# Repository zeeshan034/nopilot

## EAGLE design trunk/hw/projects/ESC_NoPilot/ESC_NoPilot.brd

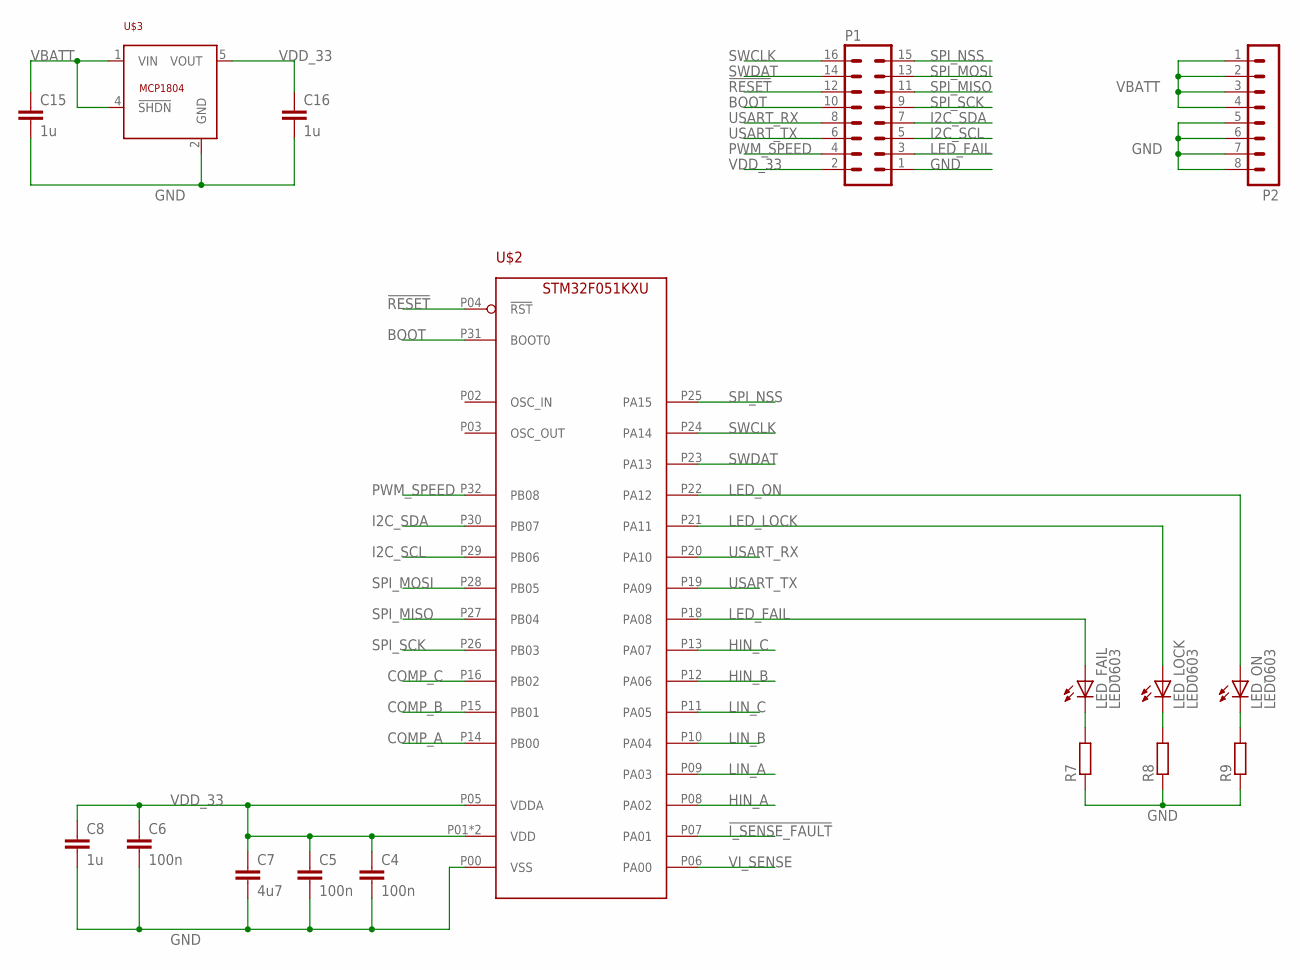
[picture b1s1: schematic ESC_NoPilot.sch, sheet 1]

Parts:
C4, C5, C6: 100n; C0402
C7: 4u7; C0805
C8, C15, C16: 1u; C0805
LED_FAIL: LED0603; D0603
LED_LOCK: LED0603; D0603
LED_ON: LED0603; D0603
P1: MA08-2
P2: MA08-1
R7, R8, R9: R-EU_R0402; R0402
U$2: STM32F051KXU; UFQFPN32
U$3: MCP1804; SOT23

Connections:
!I_SENSE_FAULT: U$2.P07 (PA01); also elsewhere on the board
!RESET: P1.12, U$2.P04 (!RST)
BOOT: P1.10, U$2.P31 (BOOT0)
COMP_A: U$2.P14 (PB00); also elsewhere on the board
COMP_B: U$2.P15 (PB01); also elsewhere on the board
COMP_C: U$2.P16 (PB02); also elsewhere on the board
GND: C4.2, C5.2, C6.2, C7.2, C8.2, C15.2, C16.2, P1.1, P2.5, P2.6, P2.7, P2.8, R7.1, R8.1, R9.1, U$2.P00 (VSS), U$3.2 (GND); also elsewhere on the board
HIN_A: U$2.P08 (PA02); also elsewhere on the board
HIN_B: U$2.P12 (PA06); also elsewhere on the board
HIN_C: U$2.P13 (PA07); also elsewhere on the board
I2C_SCL: P1.5, U$2.P29 (PB06)
I2C_SDA: P1.7, U$2.P30 (PB07)
LED_FAIL: LED_FAIL.A, P1.3, U$2.P18 (PA08)
LED_LOCK: LED_LOCK.A, U$2.P21 (PA11)
LED_ON: LED_ON.A, U$2.P22 (PA12)
LIN_A: U$2.P09 (PA03); also elsewhere on the board
LIN_B: U$2.P10 (PA04); also elsewhere on the board
LIN_C: U$2.P11 (PA05); also elsewhere on the board
unnamed: LED_FAIL.C, R7.2
unnamed: LED_LOCK.C, R8.2
unnamed: LED_ON.C, R9.2
PWM_SPEED: P1.4, U$2.P32 (PB08)
SPI_MISO: P1.11, U$2.P27 (PB04)
SPI_MOSI: P1.13, U$2.P28 (PB05)
SPI_NSS: P1.15, U$2.P25 (PA15)
SPI_SCK: P1.9, U$2.P26 (PB03)
SWCLK: P1.16, U$2.P24 (PA14)
SWDAT: P1.14, U$2.P23 (PA13)
USART_RX: P1.8, U$2.P20 (PA10)
USART_TX: P1.6, U$2.P19 (PA09)
VBATT: C15.1, P2.1, P2.2, P2.3, P2.4, U$3.1 (VIN), U$3.4 (!SHDN); also elsewhere on the board
VDD_33: C4.1, C5.1, C6.1, C7.1, C8.1, C16.1, P1.2, U$2.P01 (VDD), U$2.P05 (VDDA), U$2.P17 (VDD), U$3.5 (VOUT); also elsewhere on the board
VI_SENSE: U$2.P06 (PA00); also elsewhere on the board

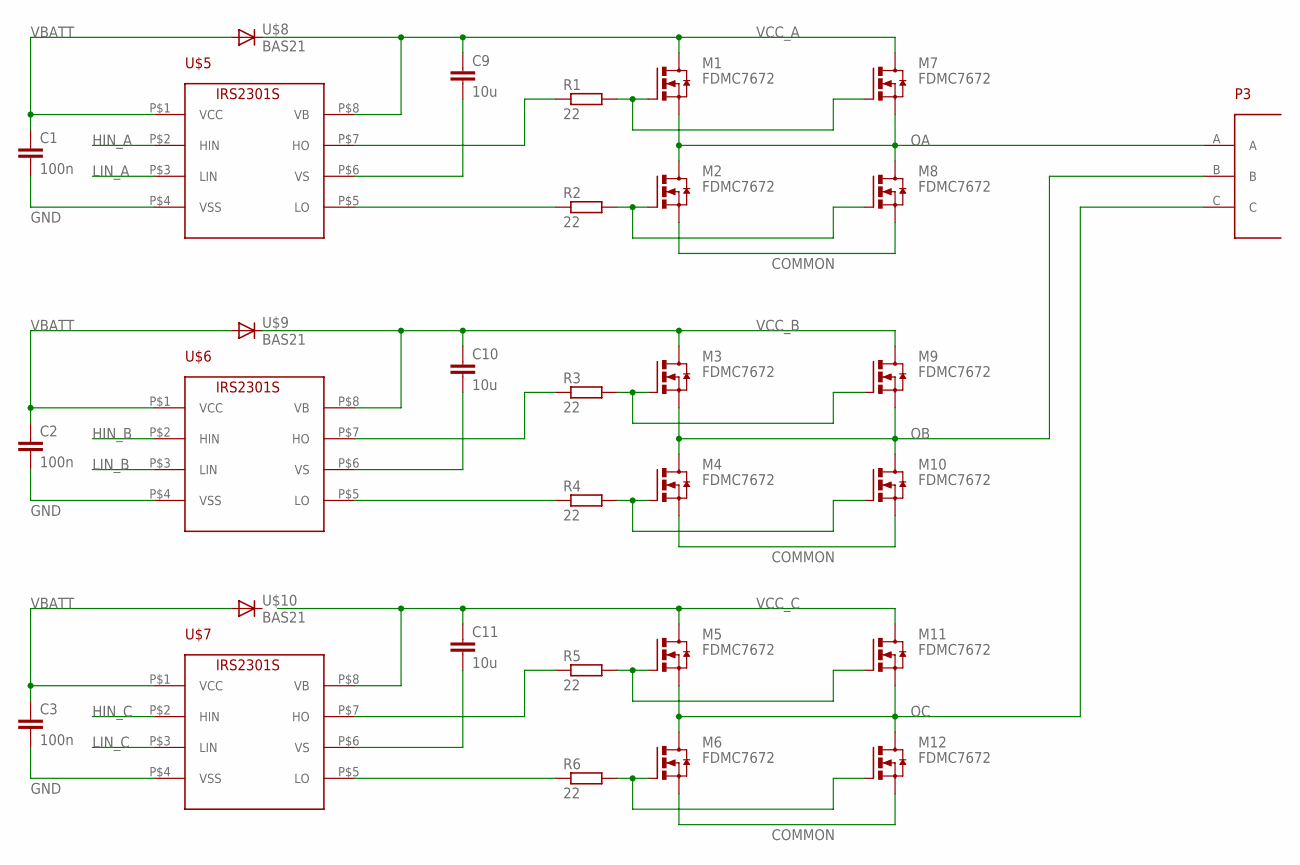
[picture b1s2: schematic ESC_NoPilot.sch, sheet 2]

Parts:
C1, C2, C3: 100n; C0402
C9, C10, C11: 10u; C0805
M1, M2, M3, M4, M5, M6, M7, M8, M9, M10, M11, M12: FDMC7672; MLP_3P3X3P3
P3: 3PH_SJ
R1, R2, R3, R4, R5, R6: 22; R0402
U$5, U$6, U$7: IRS2301S; SOIC8
U$8, U$9, U$10: BAS21; SOT23-3

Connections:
COMMON: M2.P1 (S), M2.P2 (S), M2.P3 (S), M4.P1 (S), M4.P2 (S), M4.P3 (S), M6.P1 (S), M6.P2 (S), M6.P3 (S), M8.P1 (S), M8.P2 (S), M8.P3 (S), M10.P1 (S), M10.P2 (S), M10.P3 (S), M12.P1 (S), M12.P2 (S), M12.P3 (S); also elsewhere on the board
GND: C1.2, C2.2, C3.2, U$5.P$4 (VSS), U$6.P$4 (VSS), U$7.P$4 (VSS); also elsewhere on the board
HIN_A: U$5.P$2 (HIN); also elsewhere on the board
HIN_B: U$6.P$2 (HIN); also elsewhere on the board
HIN_C: U$7.P$2 (HIN); also elsewhere on the board
LIN_A: U$5.P$3 (LIN); also elsewhere on the board
LIN_B: U$6.P$3 (LIN); also elsewhere on the board
LIN_C: U$7.P$3 (LIN); also elsewhere on the board
M1: M1.P4 (G), M7.P4 (G), R1.2
M4: M4.P4 (G), M10.P4 (G), R4.2
unnamed: C9.2, U$5.P$6 (VS)
unnamed: R1.1, U$5.P$7 (HO)
unnamed: M2.P4 (G), M8.P4 (G), R2.2
unnamed: R2.1, U$5.P$5 (LO)
unnamed: C10.2, U$6.P$6 (VS)
unnamed: M3.P4 (G), M9.P4 (G), R3.2
unnamed: R3.1, U$6.P$7 (HO)
unnamed: R4.1, U$6.P$5 (LO)
unnamed: C11.2, U$7.P$6 (VS)
unnamed: R5.1, U$7.P$7 (HO)
unnamed: M5.P4 (G), M11.P4 (G), R5.2
unnamed: M6.P4 (G), M12.P4 (G), R6.2
unnamed: R6.1, U$7.P$5 (LO)
OA: M1.P1 (S), M1.P2 (S), M1.P3 (S), M2.P0 (D), M2.P5 (D), M2.P6 (D), M2.P7 (D), M2.P8 (D), M7.P1 (S), M7.P2 (S), M7.P3 (S), M8.P0 (D), M8.P5 (D), M8.P6 (D), M8.P7 (D), M8.P8 (D), P3.A; also elsewhere on the board
OB: M3.P1 (S), M3.P2 (S), M3.P3 (S), M4.P0 (D), M4.P5 (D), M4.P6 (D), M4.P7 (D), M4.P8 (D), M9.P1 (S), M9.P2 (S), M9.P3 (S), M10.P0 (D), M10.P5 (D), M10.P6 (D), M10.P7 (D), M10.P8 (D), P3.B; also elsewhere on the board
OC: M5.P1 (S), M5.P2 (S), M5.P3 (S), M6.P0 (D), M6.P5 (D), M6.P6 (D), M6.P7 (D), M6.P8 (D), M11.P1 (S), M11.P2 (S), M11.P3 (S), M12.P0 (D), M12.P5 (D), M12.P6 (D), M12.P7 (D), M12.P8 (D), P3.C; also elsewhere on the board
VBATT: C1.1, C2.1, C3.1, U$5.P$1 (VCC), U$6.P$1 (VCC), U$7.P$1 (VCC), U$8.P1 (A), U$9.P1 (A), U$10.P1 (A); also elsewhere on the board
VCC_A: C9.1, M1.P0 (D), M1.P5 (D), M1.P6 (D), M1.P7 (D), M1.P8 (D), M7.P0 (D), M7.P5 (D), M7.P6 (D), M7.P7 (D), M7.P8 (D), U$5.P$8 (VB), U$8.P3 (C)
VCC_B: C10.1, M3.P0 (D), M3.P5 (D), M3.P6 (D), M3.P7 (D), M3.P8 (D), M9.P0 (D), M9.P5 (D), M9.P6 (D), M9.P7 (D), M9.P8 (D), U$6.P$8 (VB), U$9.P3 (C)
VCC_C: C11.1, M5.P0 (D), M5.P5 (D), M5.P6 (D), M5.P7 (D), M5.P8 (D), M11.P0 (D), M11.P5 (D), M11.P6 (D), M11.P7 (D), M11.P8 (D), U$7.P$8 (VB)

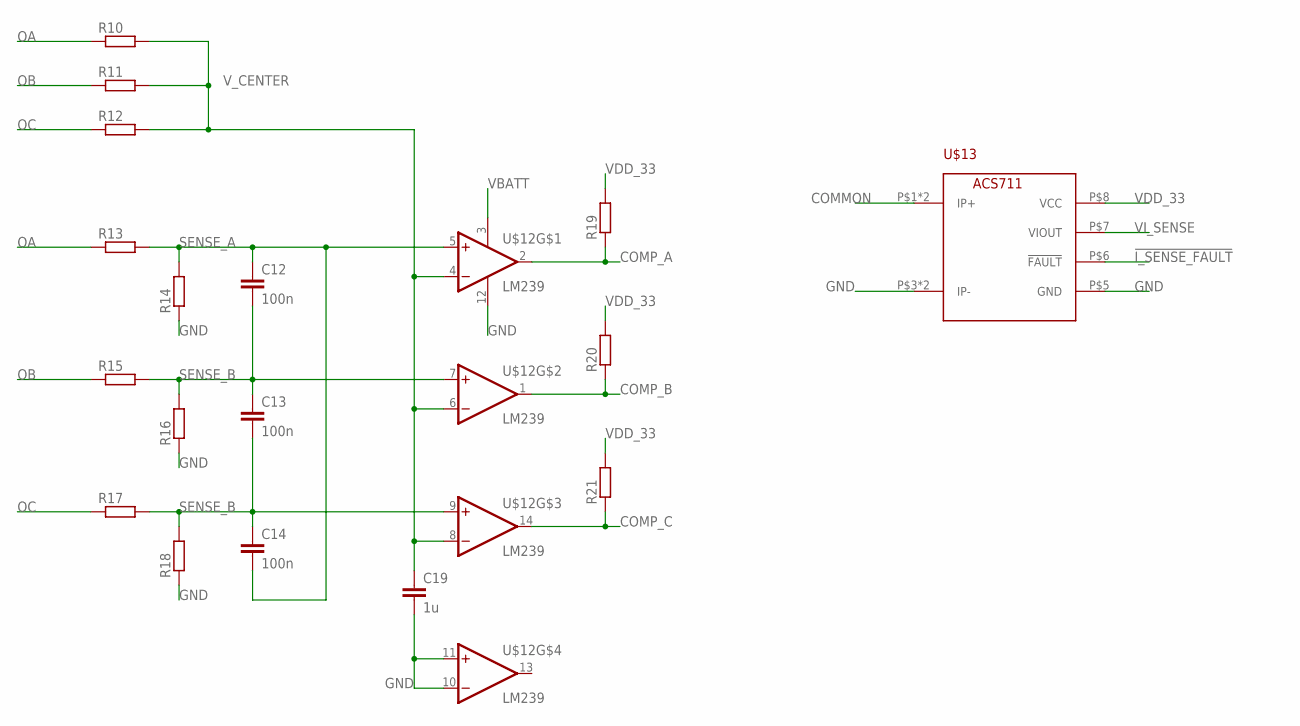
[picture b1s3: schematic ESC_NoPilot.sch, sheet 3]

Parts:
C12, C13, C14: 100n; C0402
C19: 1u; C0805
R10, R11, R12, R13, R14, R15, R16, R17, R18, R19, R20, R21: R-EU_R0402; R0402
U$12: LM239; TSSOP14
U$13: ACS711; SOIC8

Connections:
!I_SENSE_FAULT: U$13.P$6 (!FAULT); also elsewhere on the board
COMMON: U$13.P$1 (IP+), U$13.P$2 (IP+); also elsewhere on the board
COMP_A: R19.1, U$12.2 (OUT); also elsewhere on the board
COMP_B: R20.1, U$12.1 (OUT); also elsewhere on the board
COMP_C: R21.1, U$12.14 (OUT); also elsewhere on the board
GND: C19.2, R14.1, R16.1, R18.1, U$12.10 (-IN), U$12.11 (+IN), U$12.12 (GND), U$13.P$3 (IP-), U$13.P$4 (IP-), U$13.P$5 (GND); also elsewhere on the board
OA: R10.1, R13.1; also elsewhere on the board
OB: R11.1, R15.1; also elsewhere on the board
OC: R12.1, R17.1; also elsewhere on the board
SENSE_A: C12.1, C14.2, R13.2, R14.2, U$12.5 (+IN)
SENSE_B: C12.2, C13.1, C13.2, C14.1, R15.2, R16.2, R17.2, R18.2, U$12.7 (+IN), U$12.9 (+IN)
VBATT: U$12.3 (V+); also elsewhere on the board
VDD_33: R19.2, R20.2, R21.2, U$13.P$8 (VCC); also elsewhere on the board
VI_SENSE: U$13.P$7 (VIOUT); also elsewhere on the board
V_CENTER: C19.1, R10.2, R11.2, R12.2, U$12.4 (-IN), U$12.6 (-IN), U$12.8 (-IN)

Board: 2 copper layers, 66 parts (0 on the bottom side), 58 nets, no tracks yet.

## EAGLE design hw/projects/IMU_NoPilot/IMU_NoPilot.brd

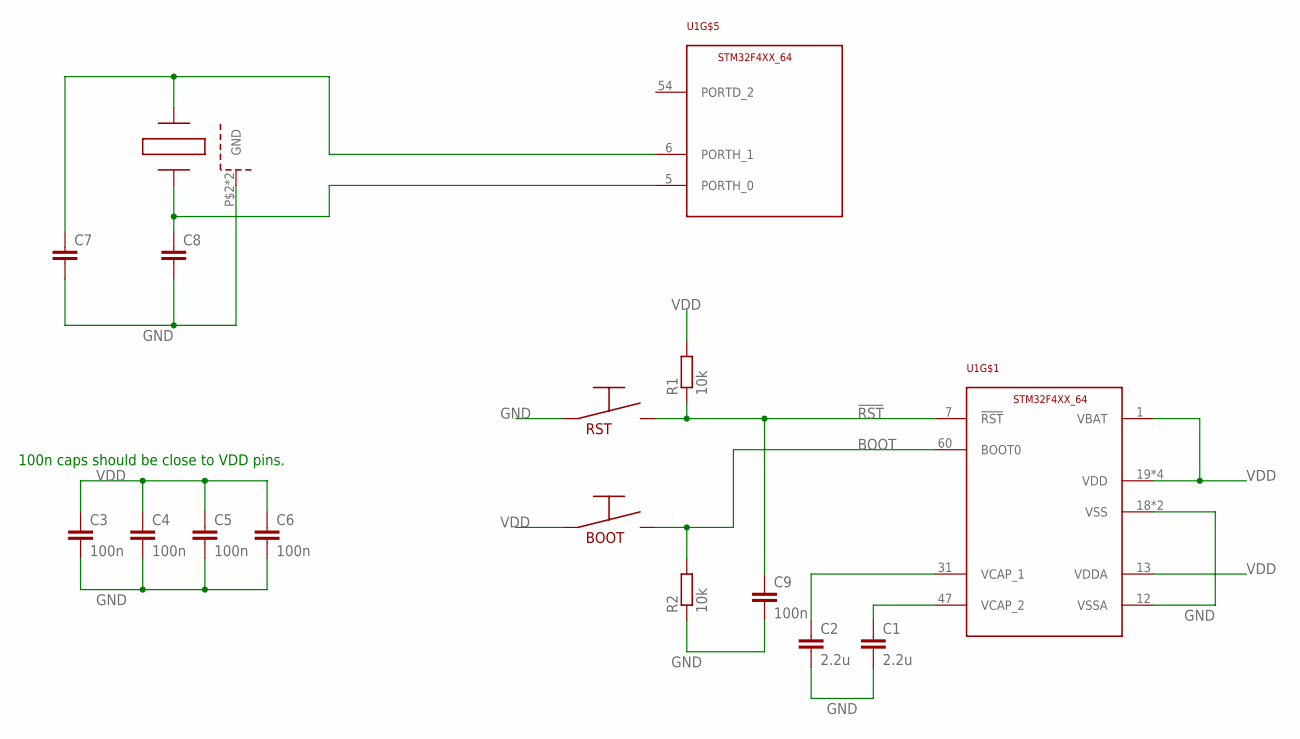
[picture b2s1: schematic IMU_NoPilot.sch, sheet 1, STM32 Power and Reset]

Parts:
BOOT: OMRON_B3FS_1000; OMROM_B3FS-1XXX
C1, C2: 2.2u; C0805
C3, C4, C5, C6, C9: 100n; C0402
C7, C8: C-EUC0402; C0402
R1, R2: 10k; R0402
RST: OMRON_B3FS_1000; OMROM_B3FS-1XXX
U1: STM32F4XX_64; TQFP64
XTAL1: XTAL_5X3P2

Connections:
!RST: C9.1, R1.1, RST.P3, RST.P4, U1.7 (!RST); also elsewhere on the board
BOOT: BOOT.P3, BOOT.P4, R2.2, U1.60 (BOOT0)
GND: C1.2, C2.2, C3.2, C4.2, C5.2, C6.2, C7.2, C8.2, C9.2, R2.1, RST.P1, RST.P2, U1.12 (VSSA), U1.18 (VSS), U1.63 (VSS), XTAL1.P$2 (GND), XTAL1.P$4 (GND); also elsewhere on the board
unnamed: C2.1, U1.31 (VCAP_1)
unnamed: C1.1, U1.47 (VCAP_2)
unnamed: C8.1, U1.5 (PORTH_0), XTAL1.P$1 (Q1)
unnamed: C7.1, U1.6 (PORTH_1), XTAL1.P$3 (Q2)
VDD: BOOT.P1, BOOT.P2, C3.1, C4.1, C5.1, C6.1, R1.2, U1.1 (VBAT), U1.13 (VDDA), U1.19 (VDD), U1.32 (VDD), U1.48 (VDD), U1.64 (VDD); also elsewhere on the board

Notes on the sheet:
100n caps should be close to VDD pins.

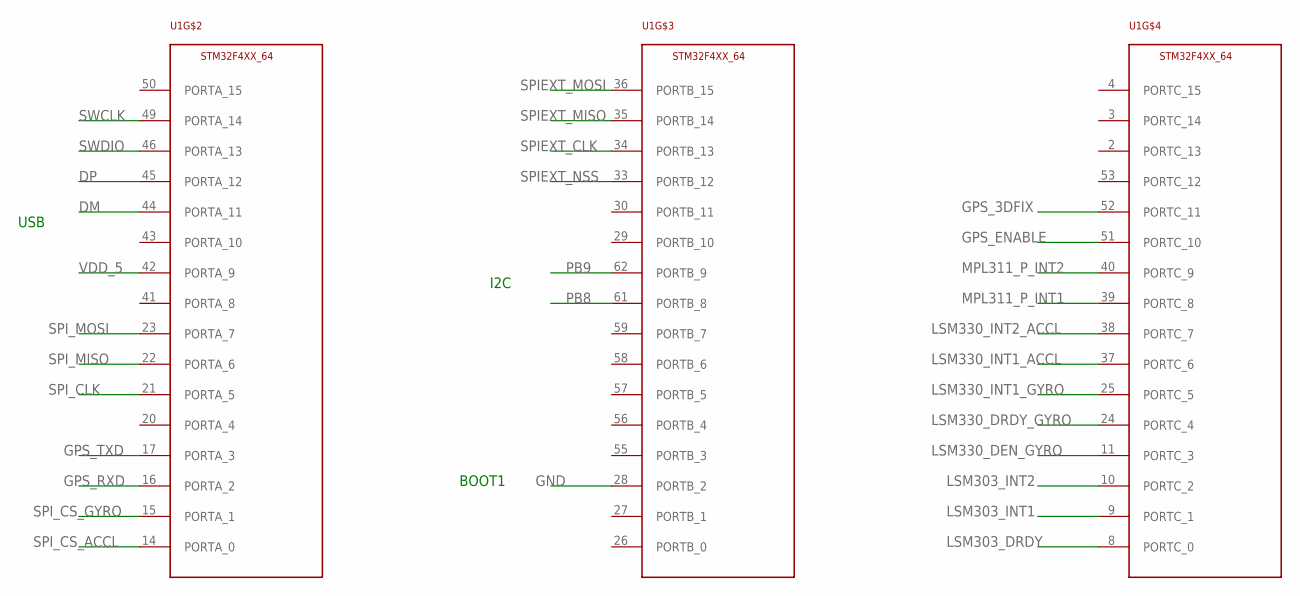
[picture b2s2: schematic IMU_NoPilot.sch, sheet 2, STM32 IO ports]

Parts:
U1: STM32F4XX_64; TQFP64

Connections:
DM: U1.44 (PORTA_11); also elsewhere on the board
DP: U1.45 (PORTA_12); also elsewhere on the board
GND: U1.28 (PORTB_2); also elsewhere on the board
GPS_3DFIX: U1.52 (PORTC_11); also elsewhere on the board
GPS_ENABLE: U1.51 (PORTC_10); also elsewhere on the board
GPS_RXD: U1.16 (PORTA_2); also elsewhere on the board
GPS_TXD: U1.17 (PORTA_3); also elsewhere on the board
LSM303_DRDY: U1.8 (PORTC_0); also elsewhere on the board
LSM303_INT1: U1.9 (PORTC_1); also elsewhere on the board
LSM303_INT2: U1.10 (PORTC_2); also elsewhere on the board
LSM330_DEN_GYRO: U1.11 (PORTC_3); also elsewhere on the board
LSM330_DRDY_GYRO: U1.24 (PORTC_4); also elsewhere on the board
LSM330_INT1_ACCL: U1.37 (PORTC_6); also elsewhere on the board
LSM330_INT1_GYRO: U1.25 (PORTC_5); also elsewhere on the board
LSM330_INT2_ACCL: U1.38 (PORTC_7); also elsewhere on the board
MPL311_P_INT1: U1.39 (PORTC_8); also elsewhere on the board
MPL311_P_INT2: U1.40 (PORTC_9); also elsewhere on the board
PB8: U1.61 (PORTB_8); also elsewhere on the board
PB9: U1.62 (PORTB_9); also elsewhere on the board
SPIEXT_CLK: U1.34 (PORTB_13); also elsewhere on the board
SPIEXT_MISO: U1.35 (PORTB_14); also elsewhere on the board
SPIEXT_MOSI: U1.36 (PORTB_15); also elsewhere on the board
SPIEXT_NSS: U1.33 (PORTB_12); also elsewhere on the board
SPI_CLK: U1.21 (PORTA_5); also elsewhere on the board
SPI_CS_ACCL: U1.14 (PORTA_0); also elsewhere on the board
SPI_CS_GYRO: U1.15 (PORTA_1); also elsewhere on the board
SPI_MISO: U1.22 (PORTA_6); also elsewhere on the board
SPI_MOSI: U1.23 (PORTA_7); also elsewhere on the board
SWCLK: U1.49 (PORTA_14); also elsewhere on the board
SWDIO: U1.46 (PORTA_13); also elsewhere on the board
VDD_5: U1.42 (PORTA_9); also elsewhere on the board

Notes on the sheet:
BOOT1
I2C
USB

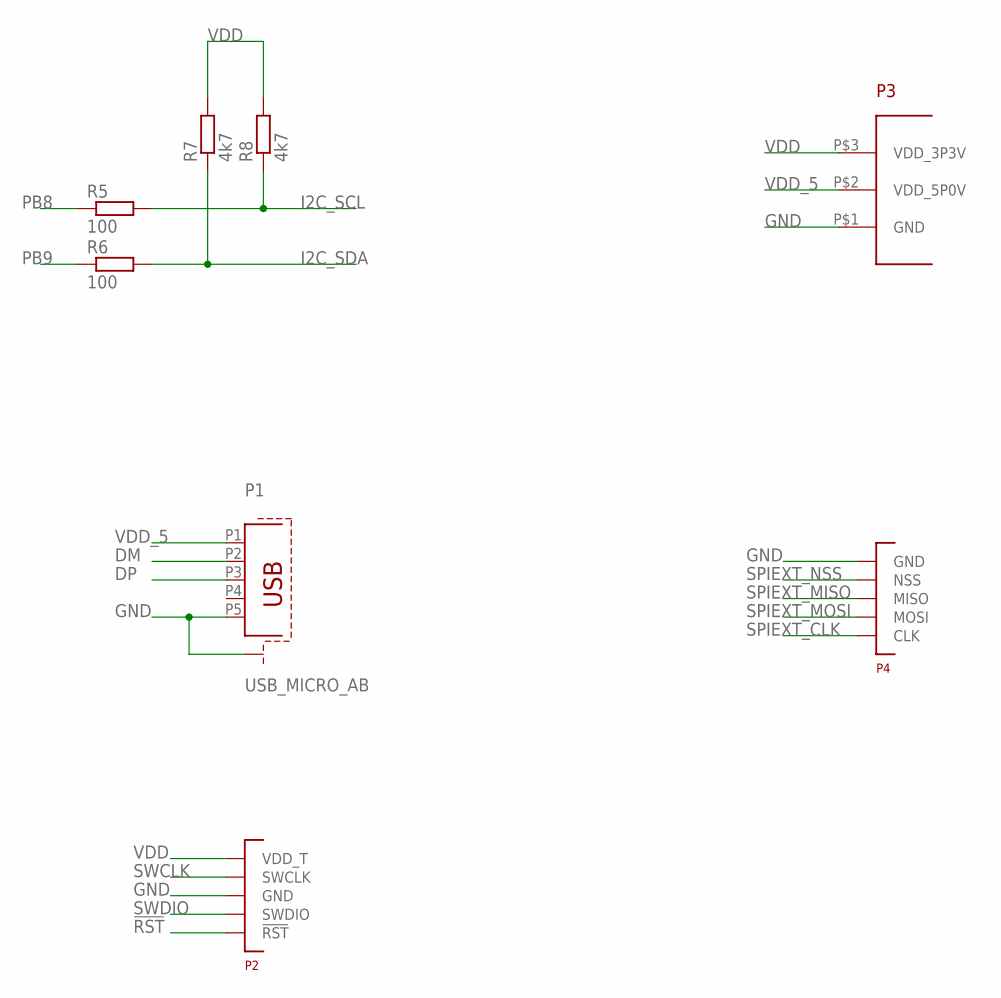
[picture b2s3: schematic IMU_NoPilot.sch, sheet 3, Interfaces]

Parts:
P1: USB_MICRO_AB
P2: ST_LINK
P3: PWR3
P4: SPI_EXT; PINLIST5_2P54
R5, R6: 100; R0402
R7, R8: 4k7; R0402

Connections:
!RST: P2.P$5 (!RST); also elsewhere on the board
DM: P1.P2 (2); also elsewhere on the board
DP: P1.P3 (3); also elsewhere on the board
GND: P1.NC1 (S1), P1.NC2 (S1), P1.NC3 (S1), P1.NC4 (S1), P1.NC5 (S1), P1.NC6 (S1), P1.P5 (5), P2.P$3 (GND), P3.P$1 (GND), P4.P$5 (GND); also elsewhere on the board
I2C_SCL: R5.2, R8.1; also elsewhere on the board
I2C_SDA: R6.2, R7.1; also elsewhere on the board
PB8: R5.1; also elsewhere on the board
PB9: R6.1; also elsewhere on the board
SPIEXT_CLK: P4.P$1 (CLK); also elsewhere on the board
SPIEXT_MISO: P4.P$3 (MISO); also elsewhere on the board
SPIEXT_MOSI: P4.P$2 (MOSI); also elsewhere on the board
SPIEXT_NSS: P4.P$4 (NSS); also elsewhere on the board
SWCLK: P2.P$2 (SWCLK); also elsewhere on the board
SWDIO: P2.P$4 (SWDIO); also elsewhere on the board
VDD: P2.P$1 (VDD_T), P3.P$3 (VDD_3P3V), R7.2, R8.2; also elsewhere on the board
VDD_5: P1.P1 (1), P3.P$2 (VDD_5P0V); also elsewhere on the board

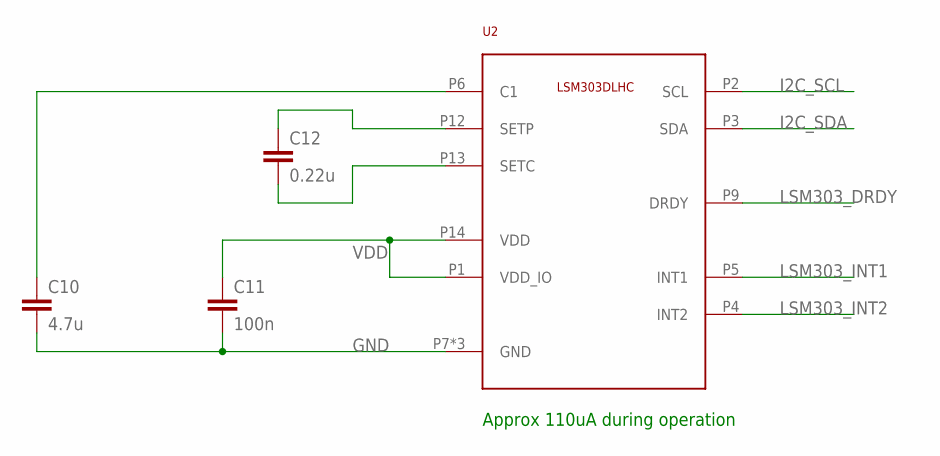
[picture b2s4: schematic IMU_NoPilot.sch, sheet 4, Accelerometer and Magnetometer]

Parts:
C10: 4.7u; C0805
C11: 100n; C0402
C12: 0.22u; C0402
U2: LSM303DLHC; LGA_3X5X1_14L

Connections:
GND: C10.2, C11.2, U2.P7 (GND), U2.P10 (GND), U2.P11 (GND); also elsewhere on the board
I2C_SCL: U2.P2 (SCL); also elsewhere on the board
I2C_SDA: U2.P3 (SDA); also elsewhere on the board
LSM303_DRDY: U2.P9 (DRDY); also elsewhere on the board
LSM303_INT1: U2.P5 (INT1); also elsewhere on the board
LSM303_INT2: U2.P4 (INT2); also elsewhere on the board
unnamed: C12.1, U2.P12 (SETP)
unnamed: C12.2, U2.P13 (SETC)
unnamed: C10.1, U2.P6 (C1)
VDD: C11.1, U2.P1 (VDD_IO), U2.P14 (VDD); also elsewhere on the board

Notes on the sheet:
Approx 110uA during operation

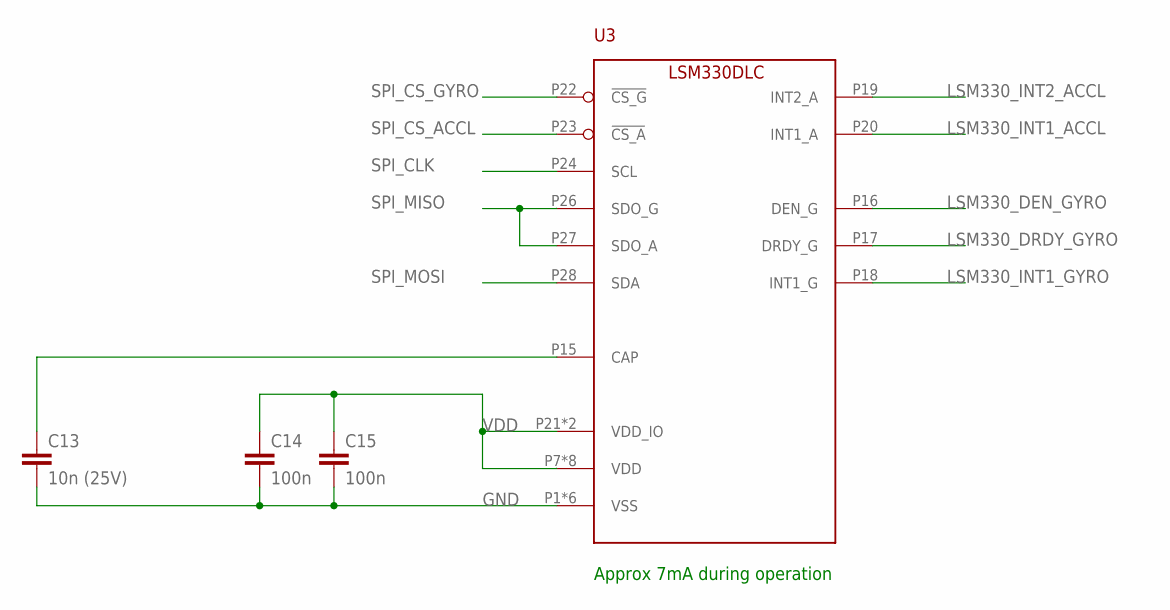
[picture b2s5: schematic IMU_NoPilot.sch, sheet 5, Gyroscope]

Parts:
C13: 10n (25V); C0402
C14, C15: 100n; C0402
U3: LSM330DLC; LGA_4X5X1P1_28L

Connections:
GND: C13.2, C14.2, C15.2, U3.P1 (VSS), U3.P2 (VSS), U3.P3 (VSS), U3.P4 (VSS), U3.P5 (VSS), U3.P6 (VSS); also elsewhere on the board
LSM330_DEN_GYRO: U3.P16 (DEN_G); also elsewhere on the board
LSM330_DRDY_GYRO: U3.P17 (DRDY_G); also elsewhere on the board
LSM330_INT1_ACCL: U3.P20 (INT1_A); also elsewhere on the board
LSM330_INT1_GYRO: U3.P18 (INT1_G); also elsewhere on the board
LSM330_INT2_ACCL: U3.P19 (INT2_A); also elsewhere on the board
unnamed: C13.1, U3.P15 (CAP)
SPI_CLK: U3.P24 (SCL); also elsewhere on the board
SPI_CS_ACCL: U3.P23 (!CS_A); also elsewhere on the board
SPI_CS_GYRO: U3.P22 (!CS_G); also elsewhere on the board
SPI_MISO: U3.P26 (SDO_G), U3.P27 (SDO_A); also elsewhere on the board
SPI_MOSI: U3.P28 (SDA); also elsewhere on the board
VDD: C14.1, C15.1, U3.P7 (VDD), U3.P8 (VDD), U3.P9 (VDD), U3.P10 (VDD), U3.P11 (VDD), U3.P12 (VDD), U3.P13 (VDD), U3.P14 (VDD), U3.P21 (VDD_IO), U3.P25 (VDD_IO); also elsewhere on the board

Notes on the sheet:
Approx 7mA during operation

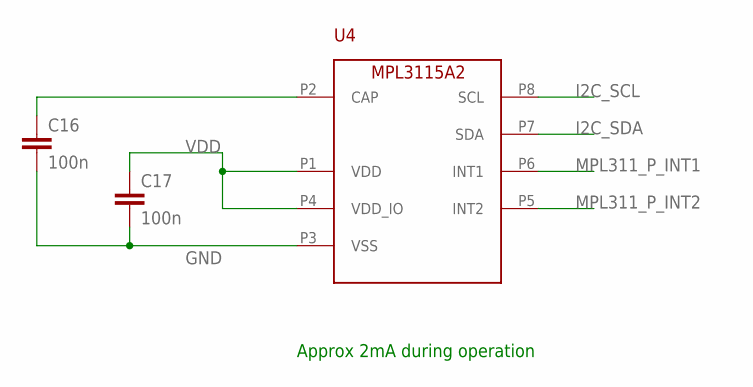
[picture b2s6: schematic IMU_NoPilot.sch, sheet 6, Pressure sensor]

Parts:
C16, C17: 100n; C0402
U4: MPL3115A2; LGA_3X5_8

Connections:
GND: C16.2, C17.2, U4.P3 (VSS); also elsewhere on the board
I2C_SCL: U4.P8 (SCL); also elsewhere on the board
I2C_SDA: U4.P7 (SDA); also elsewhere on the board
MPL311_P_INT1: U4.P6 (INT1); also elsewhere on the board
MPL311_P_INT2: U4.P5 (INT2); also elsewhere on the board
unnamed: C16.1, U4.P2 (CAP)
VDD: C17.1, U4.P1 (VDD), U4.P4 (VDD_IO); also elsewhere on the board

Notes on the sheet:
Approx 2mA during operation

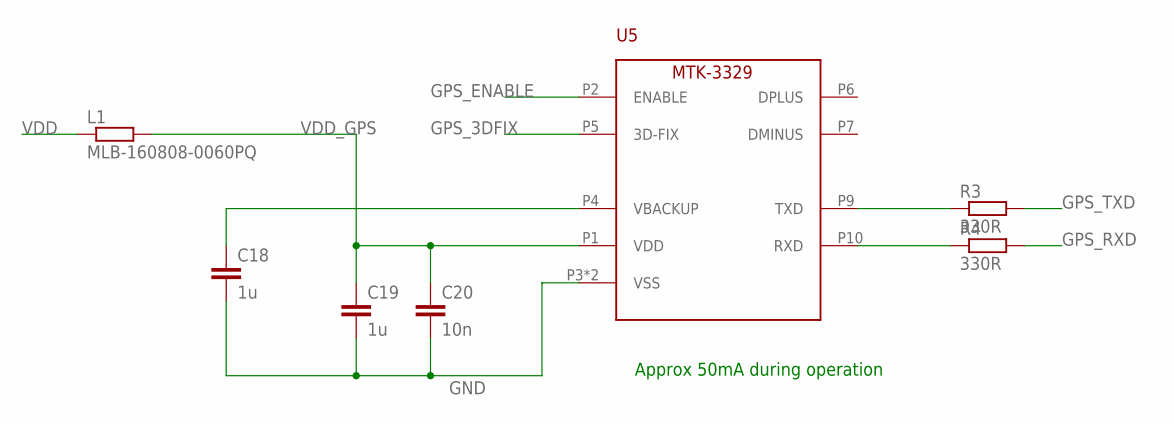
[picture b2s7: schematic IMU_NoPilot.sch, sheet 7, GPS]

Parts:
C18, C19: 1u; C0805
C20: 10n; C0402
L1: MLB-160808-0060PQ; R0603
R3, R4: 330R; R0402
U5: MTK-3329

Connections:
GND: C18.2, C19.2, C20.2, U5.P3 (VSS), U5.P8 (VSS); also elsewhere on the board
GPS_3DFIX: U5.P5 (3D-FIX); also elsewhere on the board
GPS_ENABLE: U5.P2 (ENABLE); also elsewhere on the board
GPS_RXD: R4.2; also elsewhere on the board
GPS_TXD: R3.2; also elsewhere on the board
unnamed: R3.1, U5.P9 (TXD)
unnamed: R4.1, U5.P10 (RXD)
unnamed: C18.1, U5.P4 (VBACKUP)
VDD: L1.1; also elsewhere on the board
VDD_GPS: C19.1, C20.1, L1.2, U5.P1 (VDD)

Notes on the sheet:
Approx 50mA during operation

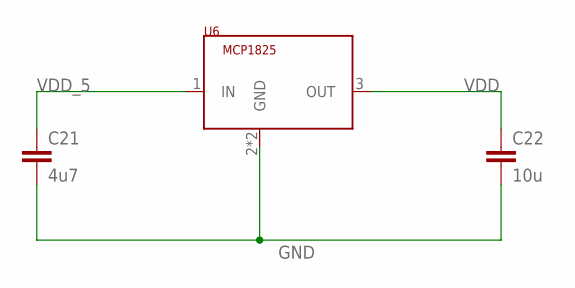
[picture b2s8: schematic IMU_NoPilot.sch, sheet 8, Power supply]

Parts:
C21: 4u7; C0805
C22: 10u; C0805
U6: MCP1825; SOT223

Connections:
GND: C21.2, C22.2, U6.2 (GND), U6.4 (GND); also elsewhere on the board
VDD: C22.1, U6.3 (OUT); also elsewhere on the board
VDD_5: C21.1, U6.1 (IN); also elsewhere on the board

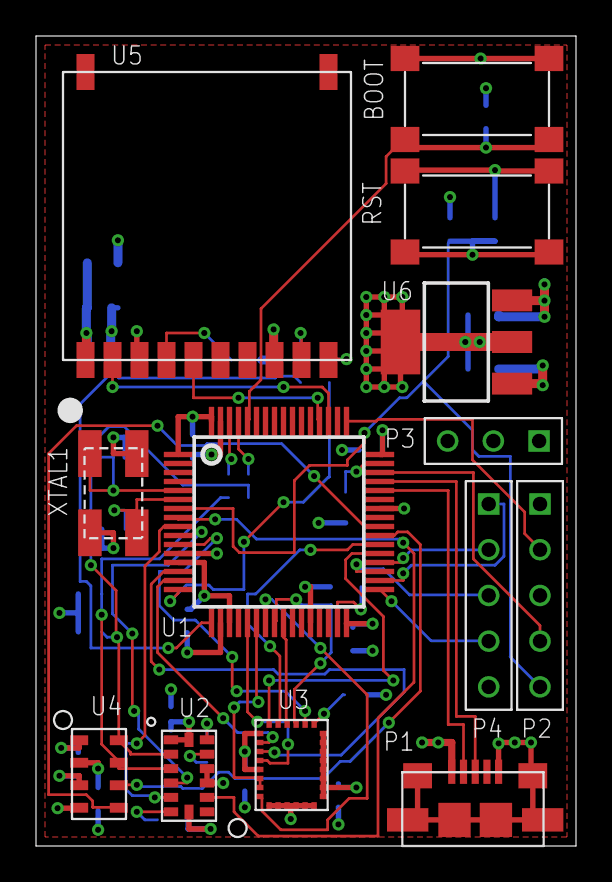
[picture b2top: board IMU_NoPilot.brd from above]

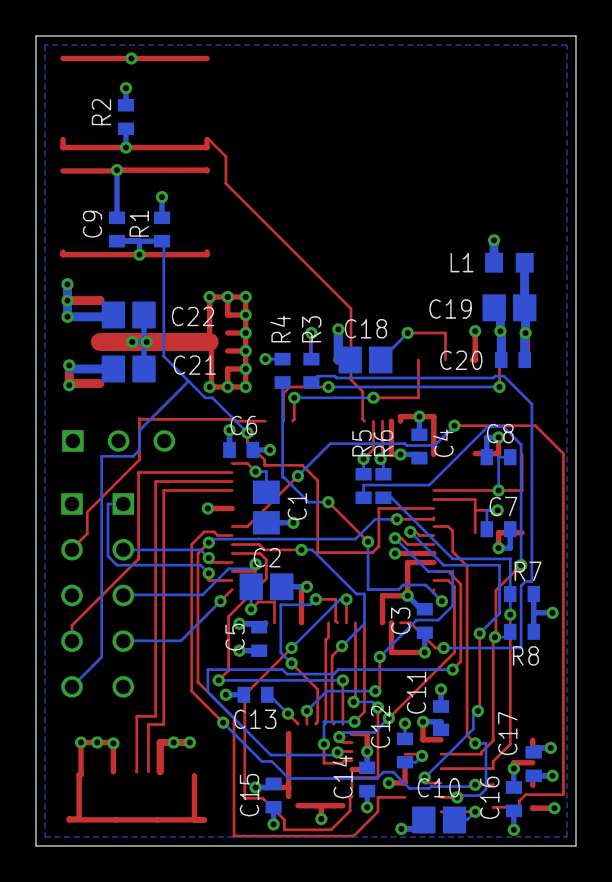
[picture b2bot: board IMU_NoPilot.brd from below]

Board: 4 copper layers, 30.0 x 45.0 mm, 44 parts (31 on the bottom side), 49 nets.

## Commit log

2012-06-20 Initial directory structure.
2012-06-20 Started on the schematics for the IMU
2012-06-20 added more libraries
2012-06-20 Finished Power and Reset part of schematics
2012-07-04 Added sensor library containing gyro accelerometer and magnetometer
2012-07-04 added accelerometer, gyro and magnetometer to schematics. Not yet connected to the uC
2012-07-04 Added absolute pressure sensor to sensor library
2012-07-05 Ready for first try at autoroute. Nothing is properly reviewed yet
2012-07-05 some manual power routing and some small adjustments to placement
2012-07-06 Changed all small caps, and all res to 0402. Large caps are 0805. Ripped all routing to start over again
2012-07-06 Cleanup of power and layout
2012-07-06 Fixed silk screen
2012-07-07 Autoroute complete. Looks good
2012-08-14 Added ESC schematics
2015-08-20 Migrating wiki contents from Google Code

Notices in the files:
hw/projects/IMU_NoPilot/IMU_NoPilot.brd:
(c) 2012 Kjell H Andersen
